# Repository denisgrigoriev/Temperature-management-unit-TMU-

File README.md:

# Temperature Management unit / Thermal management unit

A low-power, localized thermal regulation module designed to keep sensitive host electronics within operating temperature limits in sub-zero environments

## Overview:

Commercial and industrial-grade electronics often suffer unpredictable behavior, clock instability, or complete failure when exposed to ambient temperatures below -40°C.
The Temperature Management Unit (TMU) is a compact PCB module mounted directly onto critical host circuit boards. It monitors ambient conditions with high precision and automatically engages a localized surface heating element to ensure stable, reliable host system operation.

 ## Key Features
- High-Accuracy Thermal Sensing: Driven by the TI TMP117, providing readings over I2C
- Smooth Thermal Regulation: Uses PWM gate driving and soft-start thermal ramping to mitigate thermal shock and mechanical stress on PCB substrates.

 ## Schematic
 - 0.1uf capacitors are used to filter high frequency noise.
 - 10uf capacitors are used to filter low frequency noise from the batteries.
 - 10k ohm resisters are used as to pullup/pulldown.
 - 4.7k ohm resisters are used to pullup (for i2c; 4.7k ohms are a standard in i2c).
 - Mosfets act like a digitally controlled switch; turning it off and on many times is used to control the temperature.

## Bill of Materials (BOM)

| Component | Cost | Source |
| :--- | :--- | :--- |
| [Adafruit TMP117 ±0.1°C High Accuracy I2C Temperature Sensor (STEMMA QT / Qwiic)](https://thepihut.com/products/adafruit-tmp117-0-1-c-high-accuracy-i2c-temperature-sensor) | £11.10 / $15.00 | The PiHut |
| [Atmel ATtiny85 20MHz](https://thepihut.com/products/atmel-attiny85-20mhz) | £2.50 / $3.38 | The PiHut |
| [2pcs AO3400A Logic Level (3.3v) MOSFET fits 2.54mm Perfboard, Breadboard, Vero](https://www.ebay.co.uk/itm/267687635215) | £1.69 / $2.28 | Ebay |
| [Resistor Packs (1/4 Watt, ±1%)(4.7k)](https://thepihut.com/products/resistor-packs) | £1 / $1.35 | The PiHut |
| [Resistor Packs (1/4 Watt, ±1%)(10k)](https://thepihut.com/products/resistor-packs) | £1 / $1.35 | The PiHut |

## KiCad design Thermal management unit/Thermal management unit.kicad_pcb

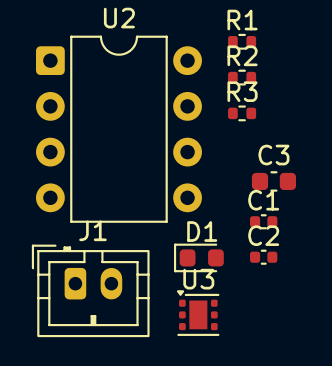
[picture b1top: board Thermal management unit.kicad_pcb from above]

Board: 2 copper layers, 10 parts (0 on the bottom side), 6 nets, no tracks yet.

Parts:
C1, C2: 0.1uf; C_0402_1005Metric
C3: 10uf; C_0603_1608Metric
D1: LED; LED_0603_1608Metric
J1: Conn_01x02_Socket; JST_PH_B2B-PH-K_1x02_P2.00mm_Vertical
R1, R2: 4.7k; R_0402_1005Metric
R3: 330; R_0402_1005Metric
U2: ATtiny85V-10P; DIP-8_W7.62mm
U3: TMP117xxDRV; WSON-6-1EP_2x2mm_P0.65mm_EP1x1.6mm

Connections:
+5V: C1.2, C2.1, C3.1, J1.1, R1.1, R2.1, U2.8 (VCC), U3.5 (V+)
GND: C1.1, C2.2, C3.2, D1.1 (K), J1.2, U2.4 (GND), U3.2 (GND), U3.4 (ADD0)
unnamed: D1.2 (A), R3.1
unnamed: R3.2, U2.2 (XTAL1/PB3)
SCL: R2.2, U2.7 (PB2), U3.1 (SCL)
SDA: R1.2, U2.5 (AREF/PB0), U3.6 (SDA)
